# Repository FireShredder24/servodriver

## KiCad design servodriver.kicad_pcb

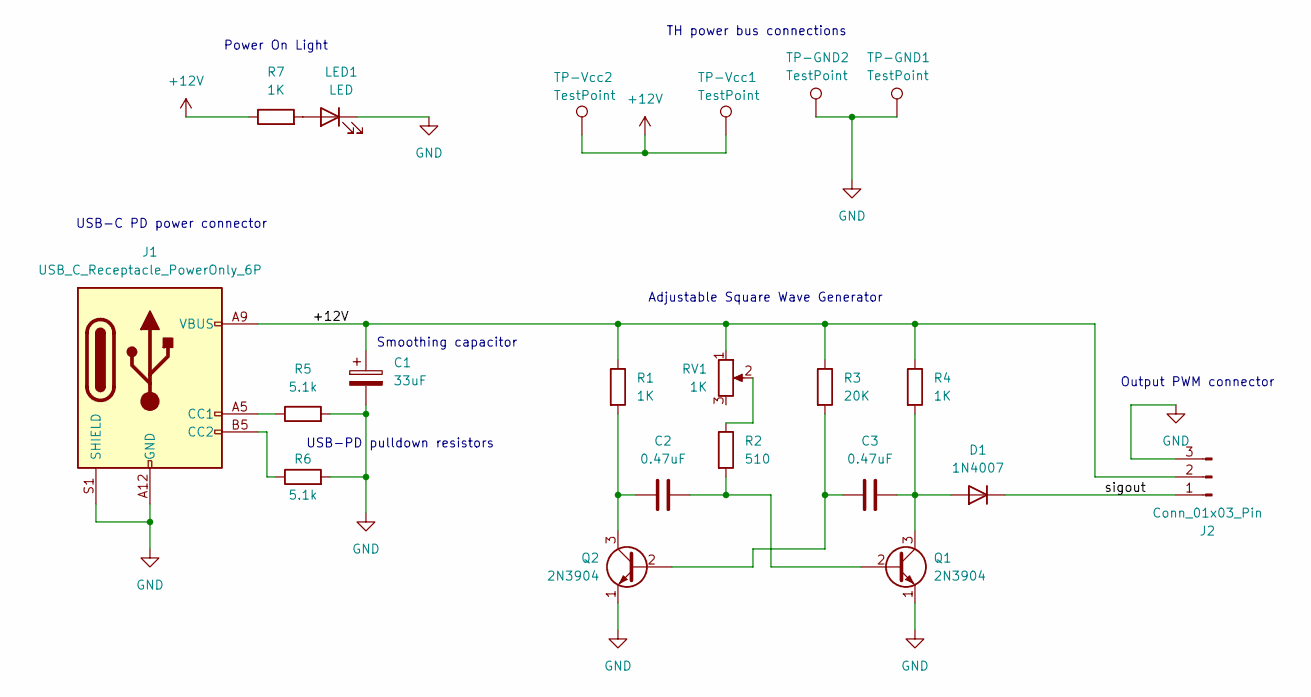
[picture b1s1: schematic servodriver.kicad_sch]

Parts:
C1: 33uF; CP_Radial_D6.3mm_P2.50mm
C2, C3: 0.47uF; C_1206_3216Metric_Pad1.33x1.80mm_HandSolder
D1: 1N4007; D_SOD-123
J1: USB_C_Receptacle_PowerOnly_6P; USB_C_Receptacle_GCT_USB4135-GF-A_6P_TopMnt_Horizontal
J2: Conn_01x03_Pin; PinHeader_1x03_P2.54mm_Horizontal
LED1: LED; LED_1210_3225Metric_Pad1.42x2.65mm_HandSolder
Q1, Q2: 2N3904; TO-92_Inline
R1, R4, R7: 1K; R_1206_3216Metric_Pad1.30x1.75mm_HandSolder
R2: 510; R_1206_3216Metric_Pad1.30x1.75mm_HandSolder
R3: 20K; R_1206_3216Metric_Pad1.30x1.75mm_HandSolder
R5, R6: 5.1k; R_1206_3216Metric_Pad1.30x1.75mm_HandSolder
RV1: 1K; Potentiometer_Alpha_RD901F-40-00D_Single_Vertical
TP-GND1, TP-GND2: TestPoint; TestPoint_THTPad_D3.0mm_Drill1.5mm
TP-Vcc1, TP-Vcc2: TestPoint; TestPoint_THTPad_D3.0mm_Drill1.5mm

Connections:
+12V: C1.1, J1.A9 (VBUS), J1.B9 (VBUS), J2.2, R1.1, R3.1, R4.1, R7.1, RV1.1, TP-Vcc1.1, TP-Vcc2.1
/sigout: D1.1 (K), J2.1
GND: C1.2, J1.A12 (GND), J1.B12 (GND), J1.S1 (SHIELD), J2.3, LED1.1 (K), Q1.1 (E), Q2.1 (E), R5.2, R6.2, TP-GND1.1, TP-GND2.1
unnamed: C3.2, D1.2 (A), Q1.3 (C), R4.2
unnamed: LED1.2 (A), R7.2
unnamed: J1.A5 (CC1), R5.1
unnamed: J1.B5 (CC2), R6.1
unnamed: C2.2, Q1.2 (B), R2.2
unnamed: C3.1, Q2.2 (B), R3.2
unnamed: C2.1, Q2.3 (C), R1.2
unnamed: R2.1, RV1.2

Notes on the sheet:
Output PWM connector
Adjustable Square Wave Generator
TH power bus connections
USB-C PD power connector
Power On Light
Smoothing capacitor
USB-PD pulldown resistors

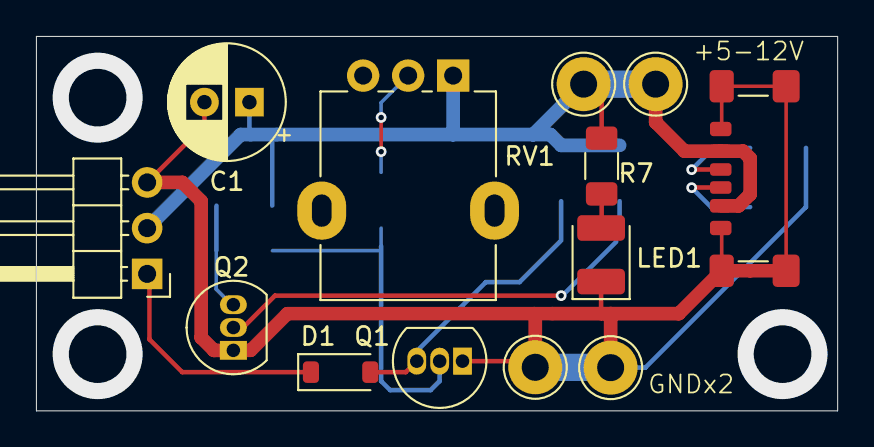
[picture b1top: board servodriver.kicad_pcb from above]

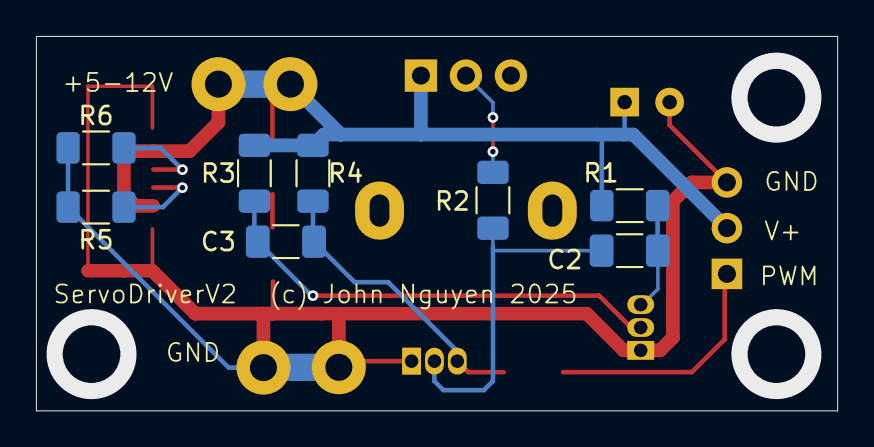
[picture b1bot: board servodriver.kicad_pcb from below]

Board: 2 copper layers, 44.5 x 20.8 mm, 21 parts (8 on the bottom side), 11 nets.

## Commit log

2025-05-01 Add all project files
